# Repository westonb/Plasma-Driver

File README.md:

# Plasma-Driver
A 40W 40.68MHz Class E RF amplifier using a MRF101AN LDMOS Device. The amplifer accepts a 40.68MHz square wave logic level input. A 5V power supply is required for the driver and a DC input of 38V is required to acheive a 40W output. 

## PCB
The PCB directory contains the kicad PCB files for the class E design and for a linear amplifier based on the 40.68MHz refrence design provided in the MRF101AN datasheet

## Schematic 
The schematics directory contains a PDF schematic of the design 

## Simulation 
The simulation directory contains a LTSpice simulation of the amplifier using a model of the MRF101AN derived from the datasheet and in-circuit testing 

## Picture

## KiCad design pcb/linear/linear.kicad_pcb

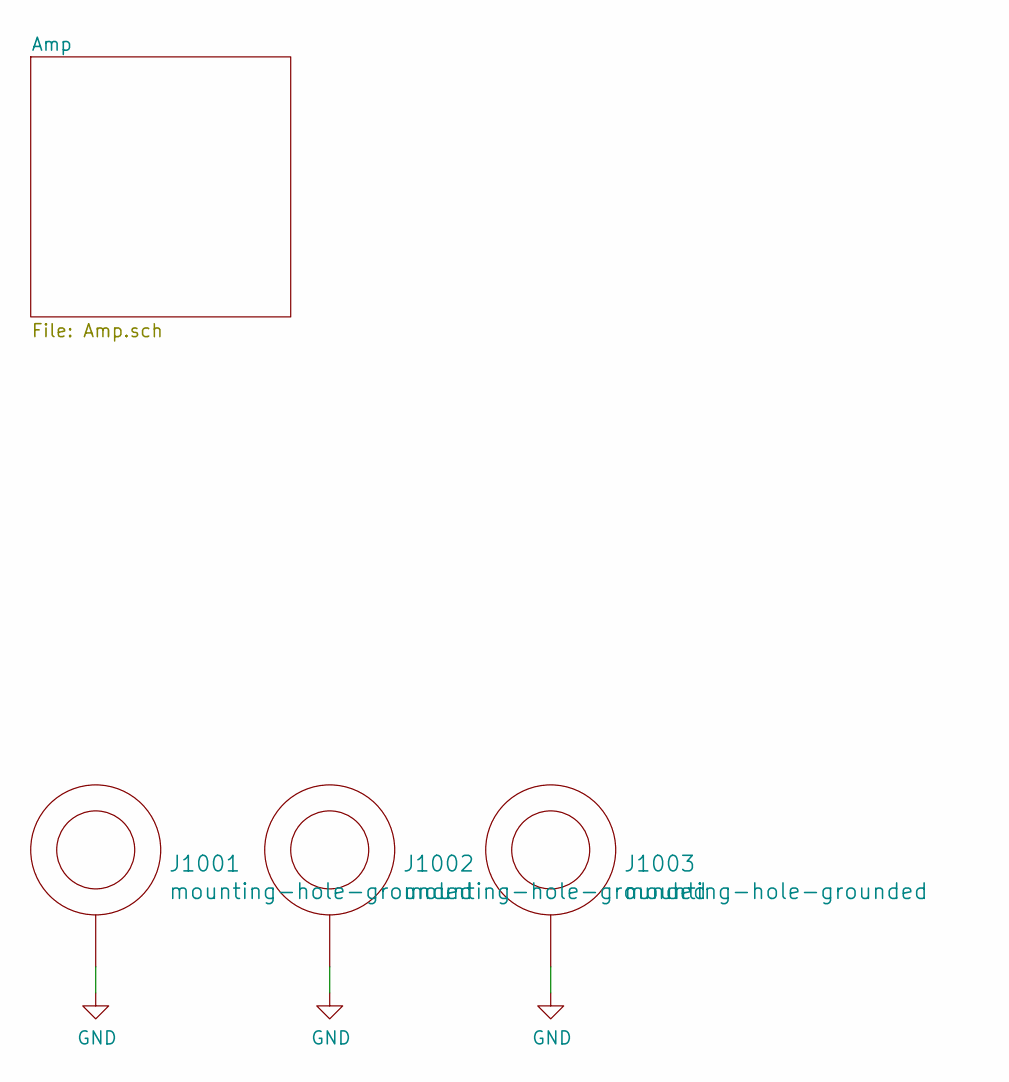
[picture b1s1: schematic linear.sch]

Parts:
J1001, J1002, J1003: mounting-hole-grounded; M3-tight-fit-socket-head

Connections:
GND: J1001.1, J1002.1, J1003.1; also elsewhere on the board

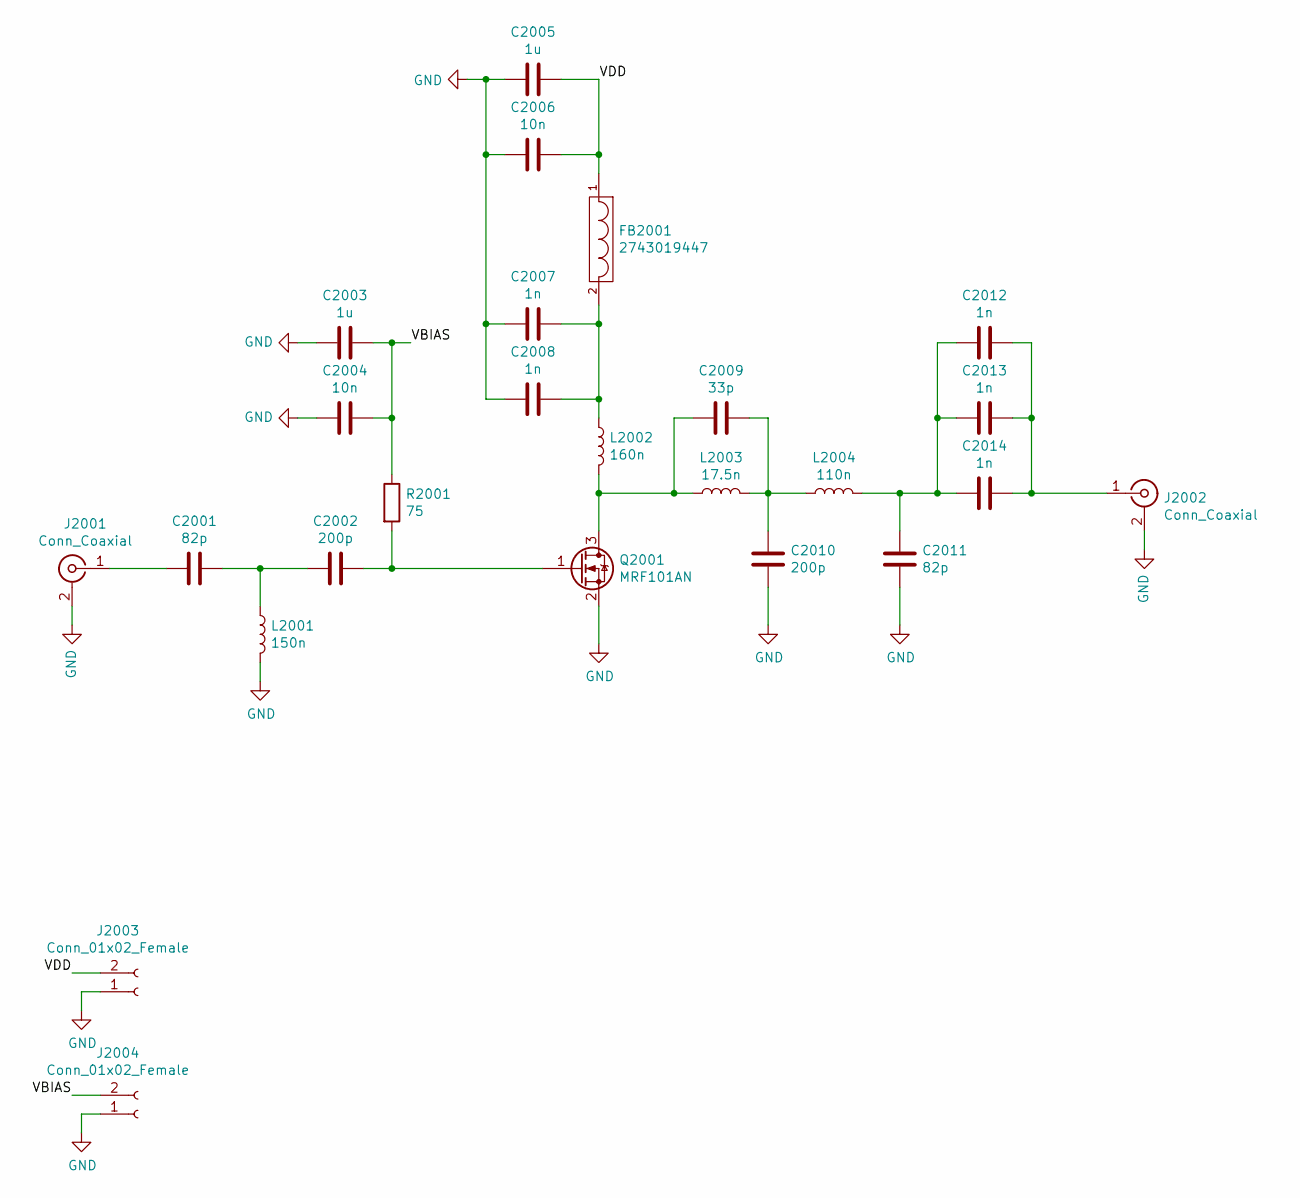
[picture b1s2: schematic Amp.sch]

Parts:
C2001, C2011: 82p; C_0805_2012Metric
C2002, C2010: 200p; C_0805_2012Metric
C2003, C2005: 1u; C_0805_2012Metric
C2004, C2006: 10n; C_0805_2012Metric
C2007, C2008, C2012, C2013, C2014: 1n; C_0805_2012Metric
C2009: 33p; C_0805_2012Metric
FB2001: 2743019447
J2001, J2002: Conn_Coaxial; SMA-Edge
J2003, J2004: Conn_01x02_Female; Terminal-block-plug_2x1_3.5mm-pitch
L2001: 150n; L_0805_2012Metric
L2002: 160n; 2222SQ-161
L2003: 17.5n; GA3095-AL
L2004: 110n; 2222SQ-111
Q2001: MRF101AN; TO-220-3_Vertical
R2001: 75; R_0805_2012Metric

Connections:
/Amp/VBIAS: C2003.2, C2004.2, J2004.2, R2001.1
/Amp/VDD: C2005.1, C2006.1, FB2001.1, J2003.2
GND: C2003.1, C2004.1, C2005.2, C2006.2, C2007.2, C2008.2, C2010.1, C2011.2, J2001.2 (Ext), J2002.2 (Ext), J2003.1, J2004.1, L2001.2, Q2001.2 (S); also elsewhere on the board
unnamed: C2001.1, C2002.2, L2001.1
unnamed: C2001.2, J2001.1 (In)
unnamed: C2002.1, Q2001.1 (G), R2001.2
unnamed: C2007.1, C2008.1, FB2001.2, L2002.1
unnamed: C2009.1, C2010.2, L2003.2, L2004.1
unnamed: C2009.2, L2002.2, L2003.1, Q2001.3 (D)
unnamed: C2011.1, C2012.2, C2013.2, C2014.2, L2004.2
unnamed: C2012.1, C2013.1, C2014.1, J2002.1 (In)

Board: 2 copper layers, 28 parts (0 on the bottom side), 11 nets, no tracks yet.

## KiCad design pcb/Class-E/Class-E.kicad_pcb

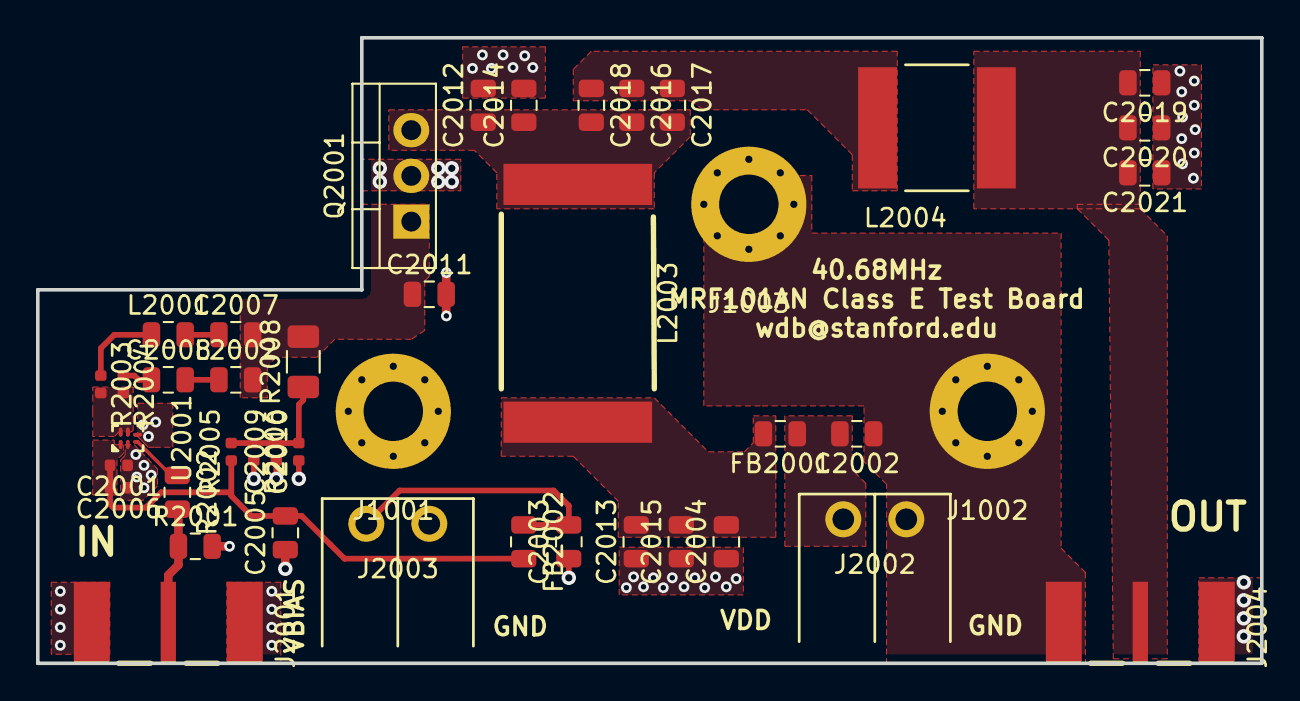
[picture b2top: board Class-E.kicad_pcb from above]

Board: 2 copper layers, 68.0 x 34.8 mm, 43 parts (0 on the bottom side), 17 nets.

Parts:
C2001, C2006, C2009: 0.1u; C_0402_1005Metric
C2002, C2003, C2005: 1u; C_0805_2012Metric
C2004, C2007, C2015: 0.1u; C_0805_2012Metric
C2008, C2011: DNP; C_0805_2012Metric
C2010: 1n; C_0402_1005Metric
C2012, C2018, C2021: 47p; C_0805_2012Metric
C2013: 1n; C_0805_2012Metric
C2014: 56p; C_0805_2012Metric
C2016, C2017: 150p; C_0805_2012Metric
C2019, C2020: 82p; C_0805_2012Metric
FB2001, FB2002: FILTER; L_0805_2012Metric
J1001, J1002, J1003: mounting-hole-grounded; M3-tight-fit-socket-head
J2001, J2004: Conn_Coaxial; SMA-Edge
J2002, J2003: Conn_01x02_Female; Terminal-block-plug_2x1_3.5mm-pitch
L2001: 100n; L_0805_2012Metric
L2002: DNP; L_0805_2012Metric
L2003: 500n; 2929SQ-501
L2004: 160n; 2222SQ-161
Q2001: MRF101AN; TO-220-3_Vertical
R2001: 50; R_0805_2012Metric
R2002: 100; R_0805_2012Metric
R2003: 1; R_0402_1005Metric
R2004: DNP; R_0402_1005Metric
R2005, R2006: 270; R_0402_1005Metric
R2008: 75; R_1206_3216Metric
U2001: LMG1020; WLCSP-6

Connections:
+5V: C2001.2, C2005.2, C2006.2, FB2002.2, R2005.1, U2001.A1
+24V: C2004.2, C2013.2, C2015.2, FB2001.2, L2003.1
/Amp/VBIAS: C2003.2, FB2002.1, J2003.2
/Amp/VDD: C2002.2, FB2001.1, J2002.2
/Amp/VOUT: C2019.2, C2020.2, C2021.2, J2004.1, L2004.2
/Amp/VSW: C2012.1, C2014.1, C2016.2, C2017.2, C2018.2, L2003.2, Q2001.3
/Amp/Vg: C2007.2, C2011.1, L2002.2, Q2001.1, R2008.2
GND: C2001.1, C2002.1, C2003.1, C2004.1, C2005.1, C2006.1, C2009.1, C2010.1, C2011.2, C2012.2, C2013.1, C2014.2, C2015.1, C2019.1, C2020.1, C2021.1, J1001.1, J1002.1, J1003.1, J2001.2, J2002.1, J2003.1, J2004.2, Q2001.2, R2001.2, R2006.2, U2001.B1, U2001.C2
unnamed: C2007.1, L2001.2
unnamed: C2008.1, R2004.1
unnamed: C2008.2, L2002.1
unnamed: C2009.2, C2010.2, R2005.2, R2006.1, R2008.1
unnamed: C2016.1, C2017.1, C2018.1, L2004.1
unnamed: J2001.1, R2001.1, R2002.2
unnamed: L2001.1, R2003.1
unnamed: R2002.1, U2001.C1
unnamed: R2003.2, R2004.2, U2001.A2, U2001.B2

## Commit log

2019-10-31 Moved files to project repo
2019-10-31 added prototype picture
2023-04-11 Added PDF of project writeup
